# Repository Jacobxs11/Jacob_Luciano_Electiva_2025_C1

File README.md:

# Jacob_Luciano_Electiva_2025_C1
Mis clases de Electiva

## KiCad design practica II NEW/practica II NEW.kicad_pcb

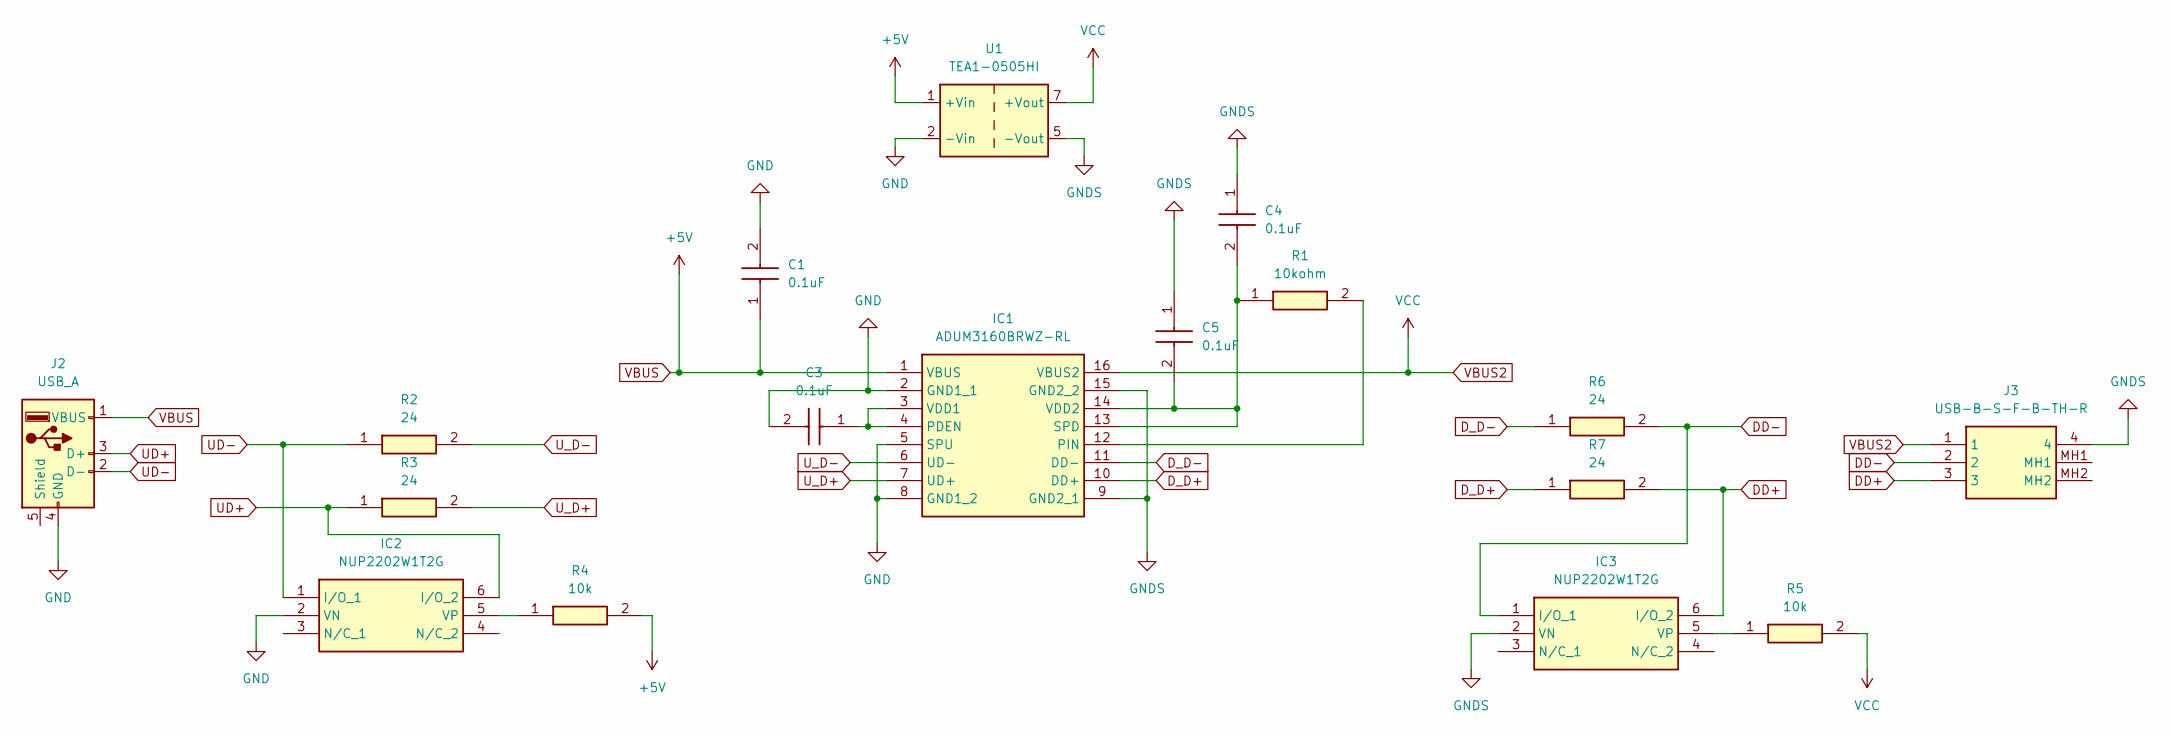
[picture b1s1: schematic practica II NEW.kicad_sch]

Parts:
C1, C3, C4, C5: 0.1uF; C0805; Manufacturer_Part_Number C0805X104K8RACAUTO; Mouser Part Number 80-C0805X104K8RAUTO
IC1: ADUM3160BRWZ-RL; SOIC127P1032X265-16N; Manufacturer_Part_Number ADUM3160BRWZ-RL; Mouser Part Number 584-ADUM3160BRWZ-R
IC2, IC3: NUP2202W1T2G; SOT65P210X110-6N; Manufacturer_Part_Number NUP2202W1T2G; Mouser Part Number 863-NUP2202W1T2G
J2: USB_A; USB_A_Molex_67643_Horizontal
J3: USB-B-S-F-B-TH-R; USBBSFBTHR; Manufacturer_Part_Number USB-B-S-F-B-TH-R; Mouser Part Number 200-USBBSFBTHR
R1: 10kohm; RESC2012X55N; Manufacturer_Part_Number TNPW080510K0FEEA; Mouser Part Number 71-TNPW080510K0FEEA
R2, R3, R6, R7: 24; RESC2012X60N; Manufacturer_Part_Number RT0805FRE0724RL
R4, R5: 10k; RESC2012X55N; Manufacturer_Part_Number TNPW080510K0FEEA; Mouser Part Number 71-TNPW080510K0FEEA
U1: TEA1-0505HI; Converter_DCDC_TRACO_TEA1-xxxxHI_THT

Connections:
DD+: IC3.6 (I/O_2), J3.3, R7.2
DD-: IC3.1 (I/O_1), J3.2, R6.2
D_D+: IC1.10 (DD+), R7.1
D_D-: IC1.11 (DD-), R6.1
GND: C1.2, C3.2, IC1.2 (GND1_1), IC1.5 (SPU), IC1.8 (GND1_2), IC2.2 (VN), J2.4 (GND), U1.2 (-Vin)
GNDS: C4.1, C5.1, IC1.9 (GND2_1), IC1.15 (GND2_2), IC3.2 (VN), J3.4, U1.5 (-Vout)
unnamed: C3.1, IC1.3 (VDD1), IC1.4 (PDEN)
unnamed: IC1.12 (PIN), R1.2
unnamed: C4.2, C5.2, IC1.13 (SPD), IC1.14 (VDD2), R1.1
unnamed: IC2.5 (VP), R4.1
unnamed: IC3.5 (VP), R5.1
UD+: IC2.6 (I/O_2), J2.3 (D+), R3.1
UD-: IC2.1 (I/O_1), J2.2 (D-), R2.1
U_D+: IC1.7 (UD+), R3.2
U_D-: IC1.6 (UD-), R2.2
VBUS: C1.1, IC1.1 (VBUS), J2.1 (VBUS), R4.2, U1.1 (+Vin)
VBUS2: IC1.16 (VBUS2), J3.1, R5.2, U1.7 (+Vout)

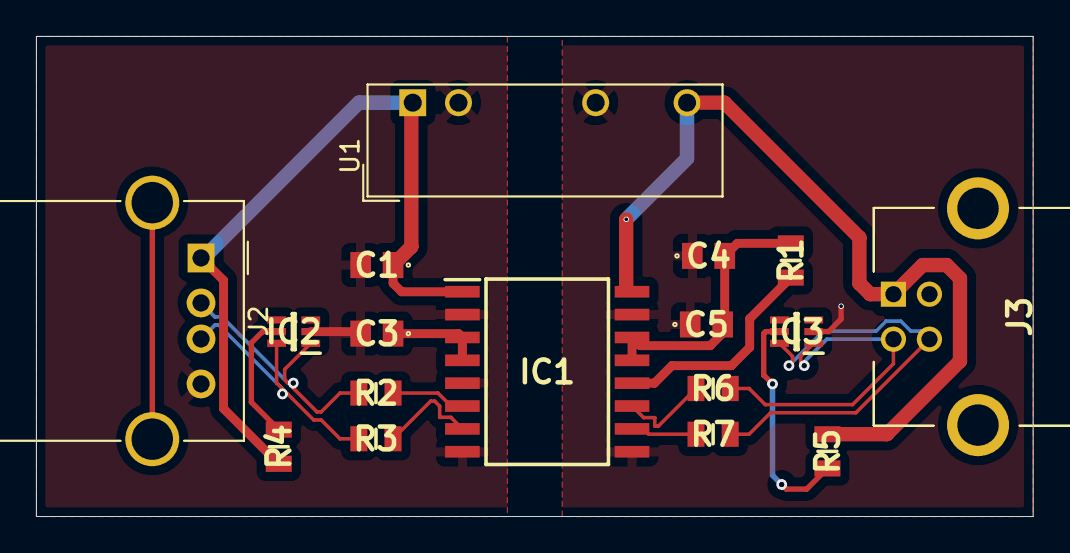
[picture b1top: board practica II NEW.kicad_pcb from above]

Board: 2 copper layers, 55.4 x 26.7 mm, 17 parts (0 on the bottom side), 17 nets.

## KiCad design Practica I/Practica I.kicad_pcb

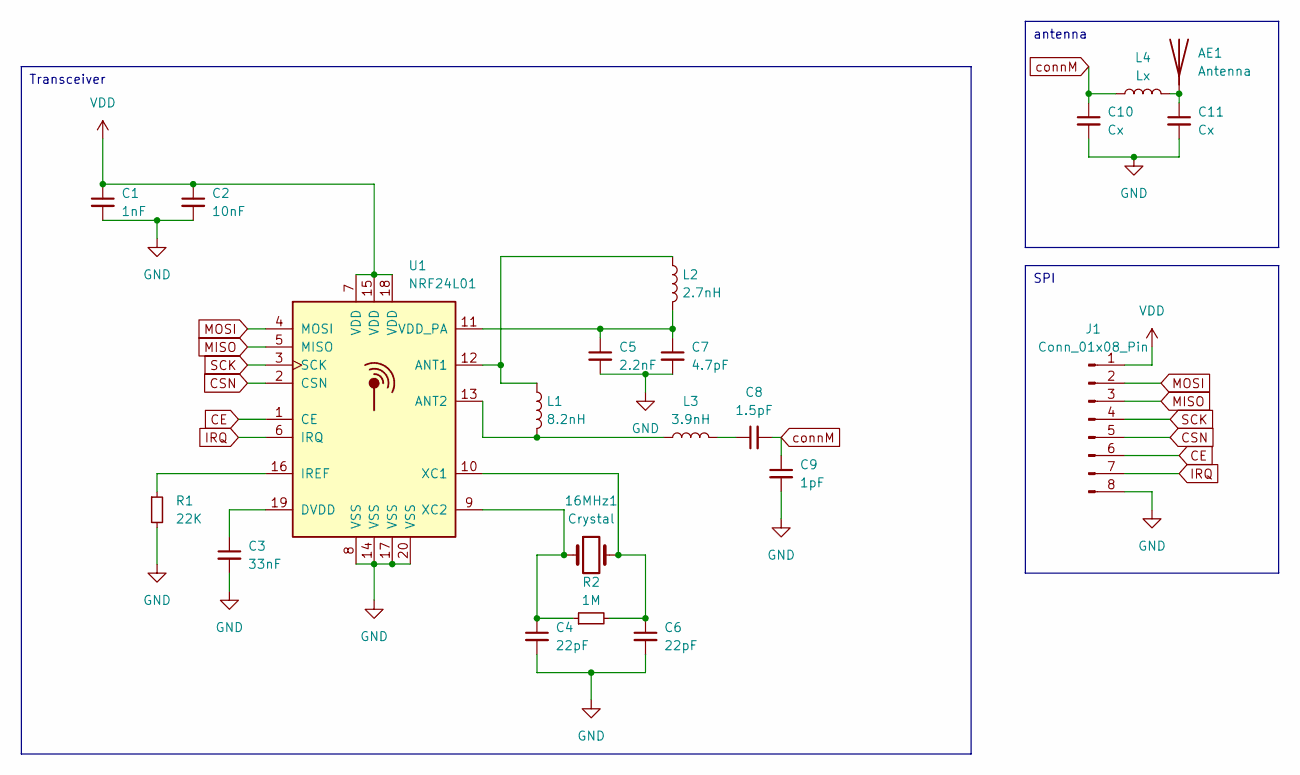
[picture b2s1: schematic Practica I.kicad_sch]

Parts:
16MHz1: Crystal; Crystal_SMD_3215-2Pin_3.2x1.5mm
AE1: Antenna; Texas_SWRA117D_2.4GHz_Right
C1: 1nF; C_0402_1005Metric
C2: 10nF; C_0402_1005Metric
C3: 33nF; C_0402_1005Metric
C4, C6: 22pF; C_0402_1005Metric
C5: 2.2nF; C_0402_1005Metric
C7: 4.7pF; C_0402_1005Metric
C8: 1.5pF; C_0402_1005Metric
C9: 1pF; C_0402_1005Metric
C10, C11: Cx; C_0402_1005Metric
J1: Conn_01x08_Pin; Hirose_DF13-08P-1.25DSA_1x08_P1.25mm_Vertical
L1: 8.2nH; L_0402_1005Metric
L2: 2.7nH; L_0402_1005Metric
L3: 3.9nH; L_0402_1005Metric
L4: Lx; L_0402_1005Metric
R1: 22K; R_0402_1005Metric
R2: 1M; R_0402_1005Metric
U1: NRF24L01; QFN-20-1EP_4x4mm_P0.5mm_EP2.5x2.5mm

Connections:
CE: J1.6, U1.1 (CE)
CSN: J1.5, U1.2 (CSN)
GND: C1.2, C2.2, C3.2, C4.2, C5.2, C6.2, C7.2, C9.2, C10.2, C11.2, J1.8, R1.2, U1.8 (VSS), U1.14 (VSS), U1.17 (VSS), U1.20 (VSS)
IRQ: J1.7, U1.6 (IRQ)
MISO: J1.3, U1.5 (MISO)
MOSI: J1.2, U1.4 (MOSI)
unnamed: AE1.1 (A), C11.1, L4.2
unnamed: C8.1, L3.2
unnamed: L1.1, L2.1, U1.12 (ANT1)
unnamed: L1.2, L3.1, U1.13 (ANT2)
unnamed: C3.1, U1.19 (DVDD)
unnamed: R1.1, U1.16 (IREF)
unnamed: C5.1, C7.1, L2.2, U1.11 (VDD_PA)
unnamed: 16MHz1.2, C6.1, R2.2, U1.10 (XC1)
unnamed: 16MHz1.1, C4.1, R2.1, U1.9 (XC2)
SCK: J1.4, U1.3 (SCK)
VDD: C1.1, C2.1, J1.1, U1.7 (VDD), U1.15 (VDD), U1.18 (VDD)
connM: C8.2, C9.1, C10.1, L4.1

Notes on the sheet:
antenna
SPI
Transceiver

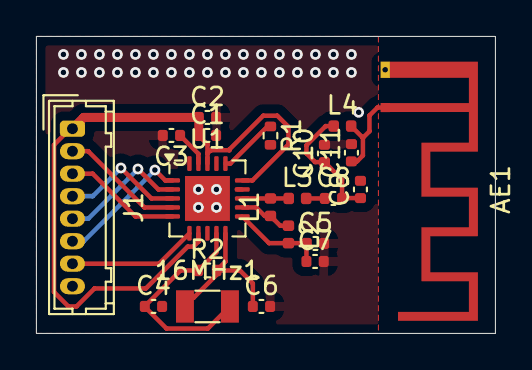
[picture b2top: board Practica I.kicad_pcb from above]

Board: 2 copper layers, 25.5 x 16.5 mm, 21 parts (0 on the bottom side), 18 nets.

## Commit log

2025-01-23 Create Proyecto 1
2025-01-23 proyecto 1
2025-01-23 Resumen 1 Matematicas para la computacion
2025-04-25 Add files via upload
    Driver Brushless motor
2025-04-25 Add files via upload
    Practica Final
